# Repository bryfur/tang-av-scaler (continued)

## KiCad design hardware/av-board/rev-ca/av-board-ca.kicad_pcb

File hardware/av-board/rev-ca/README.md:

# AV board rev C-A

The Tang Mega 138K SOM on its own carrier, HDMI from an ADV7511 at up to 1080p60 (rev B's, fed
24-bit RGB 4:4:4). Everything else is shared with rev C-B: [../rev-c/design.md](../rev-c/design.md)
describes both.

Status: designed, reviewed against the data sheets ([../rev-c/review.md](../rev-c/review.md) for
the parts rev C adds; rev B's circuits, shared, in [../rev-b/review.md](../rev-b/review.md)), placed
and routed: DRC clean, no unconnected items, fab files made; not ordered.

- `board.py`: the parts and nets (the shared circuit in ../rev-c/carrier.py and ../kit/circuits.py)
- `gen_pcb.py`: the PCB (../rev-c/layout.py, kit/)
- `fpga/av-board-ca.cst`: the FPGA pin assignment, Gowin constraints, generated from the board

## Ordering at JLCPCB

As rev B ([../rev-b/README.md](../rev-b/README.md)): `fab/` holds the Gerbers and the BOM/CPL, and a
`hand-jacks` BOM/CPL leaves the six RCA jacks for hand soldering. Settings the files do not carry:

- 4 layers, 1.6 mm, stack-up **JLC04161H-7628** (F.Cu / In1 GND / In2 GND / B.Cu), impedance
  control on: the TMDS pairs 0.25 mm lines 0.25 mm apart on F.Cu over In1, 103 R differential by
  IPC-2141, as rev B; confirm in JLCPCB's impedance calculator. The HDMI lines follow TI's
  layout rules (SPRAAR7: ../rev-c/review.md's HDMI rows, checked by `kit/hdmi_audit.py rev-ca`);
  the voids in In1 and In2 under the ESD arrays' TMDS pads are meant.
- Minimum clearance 0.1 mm (the USB-C receptacle's own GND/VBUS pads; JLCPCB's four-layer minimum
  is 0.09 mm); 0.4/0.2 mm vias at the SOM receptacles' ground pads and the ESD arrays.
- Top-side assembly only. Fitted by hand: the SOM's four M2 x 3 mm spacers and M2 screws, the XIAO
  ESP32-S3 (in its sockets J11/J12, its USB-C towards the board's bottom edge: silkscreen
  "XIAO, USB >" beside J12; a C3 works too, JTAG over Wi-Fi only), and the jacks
  for the `hand-jacks` variant.
- Power from a 5 V / 3 A USB-C supply (the board and SOM draw up to about 2 A; a sink with only
  5.1 k on CC cannot ask a weaker source for less). J16 (JTAG) is for a cable with the XIAO out of
  its sockets.
- Check in JLCPCB's preview: the SOM receptacles J20-J22 on their pads (JLCPCB's footprint numbers
  them as a mirror of ours, so its pin 1 dot shows at the far end of the row: the DF40 has no
  polarity [Hirose DF40 drawings], either way is right; do not turn them), the USB-C (mouth out
  of the back edge), the chips' rotations, the RCA jacks' barrels over the back
  edge (the CPL turns the yellow and orange ones 90 degrees for JLCPCB's footprint, kit/gen_fab.py
  JLC_TURN; the red RCJ-012 has no model there and is placed as drawn, as the black RCJ-011).

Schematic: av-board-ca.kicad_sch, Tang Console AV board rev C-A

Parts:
C1, C2: 47u; C_1206_3216Metric; LCSC C96123
C3, C20, C21, C22, C27, C28, C30, C33, C36, C38, C41, C42, C43, C44, C45, C47, C49, C51, C53, C55, C58, C60, C62, C68, C69, C70, C71, C72, C74, C75, C76, C77, C78, C81, C82, C86, C87, C88, C89, C90, C91, C92, C93, C94, C95, C96: 100n; C_0402_1005Metric; LCSC C1525
C4, C6, C7, C9, C10, C12, C13, C15, C73: 10u; C_0805_2012Metric; LCSC C15850
C5: 6.8p; C_0402_1005Metric; LCSC C1576
C8, C11, C14, C64, C66: 220p; C_0402_1005Metric; LCSC C1530
C16, C17, C18, C19, C59, C61, C63, C80, C83, C84, C85: 10u; C_0603_1608Metric; LCSC C19702
C23, C24: 1n; C_0402_1005Metric; LCSC C1523
C25, C26: 33p; C_0402_1005Metric; LCSC C1562
C29, C32, C35, C37: 10u; C_0402_1005Metric; LCSC C15525
C31, C34, C40, C46, C48, C50, C52, C54, C56: 10n; C_0402_1005Metric; LCSC C15195
C39: 82n; C_0402_1005Metric; LCSC C277511
C57, C65, C67, C79: 1u; C_0603_1608Metric; LCSC C15849
C97, C98, C99, C100: 22u; C_0805_2012Metric; LCSC C45783
D1, D3: B5819W; D_SOD-123; LCSC C8598
D2, D4, D5: KT-0603R; LED-SMD_L1.6-W0.8-R-RD; LCSC C2286
D6: SMF5.0A; D_SMF; LCSC C2857263
D7: 1N4148WS; D_SOD-323; LCSC C2128
D8, D9, D10, D11, D12, D13: TPD1E05U06DPYR; X1SON-2_L1.0-W0.6-P0.65-RD-1; LCSC C436349
F1: 3A; Fuse_1812_4532Metric; LCSC C18198349
F2, F3: 0.2A; F0805; LCSC C883105
FB1, FB2, FB3, FB4: 120R; L_0603_1608Metric; LCSC C14709
J1: RCA Y; CONN-TH_RCJ-011; LCSC C4991844
J2: RCA Pb; CONN-TH_RCJ-011; LCSC C4991844
J3: RCA Pr; CONN-TH_RCJ-011; LCSC C4991691
J4: RCA L; CONN-TH_RCJ-011; LCSC C4991844
J5: RCA R; CONN-TH_RCJ-011; LCSC C4991691
J6: HDMI-001; HDMI-SMD_19P-P0.50-H-F; LCSC C138388
J7: SYNC; HDR-TH_2P-P2.54-V-M; LCSC C492401
J8: VGA; HDR-TH_16P-P2.54-V-M-R2-C8-S2.54; LCSC C68234
J11: XIAO 5V..D7; HDR-TH_7P-P2.54-V-F; LCSC C22438157
J12: XIAO D0..D6; HDR-TH_7P-P2.54-V-F; LCSC C22438157
J13: OPTICAL; HDR-TH_3P-P2.54-V-M_PZ254V-11-03P; LCSC C2937625
J14: RCA S/PDIF; CONN-TH_RCJ-011; LCSC C22359757
J15: USB-C 5V; USB-C_SMD-TYPE-C-31-M-12_1; LCSC C165948
J16: JTAG; HDR-TH_6P-P2.54-V-M; LCSC C492405
J20: DF40HC(3.0)-80DS; DF40HC-3.0-80DS-SOM; LCSC C2858577
J21, J22: DF40HC(3.0)-100DS; DF40HC-3.0-100DS-SOM; LCSC C424649
L1: 2.2uH; IND-SMD_L3.0-W3.0_FNR30XXS; LCSC C167747
L2, L3, L4: 10uH; IND-SMD_L4.0-W4.0_SMNR4012; LCSC C222882
Q1, Q2, Q3, Q4: 2N7002; SOT-23-3_L2.9-W1.3-P1.90-LS2.4-BR; LCSC C8545
R1, R2, R101, R102: 5.1k; R_0402_1005Metric; LCSC C25905
R3: 499k; R_0402_1005Metric; LCSC C25793
R4, R53, R55: 100k; R_0402_1005Metric; LCSC C25741
R5: 169k; R_0402_1005Metric; LCSC C25758
R6, R8, R10: 30.1k; R_0402_1005Metric; LCSC C29402
R7, R9: 78.7k; R_0402_1005Metric; LCSC C67239
R11, R12, R13, R14, R32, R33, R34, R50: 75; R_0603_1608Metric; LCSC C4275
R15, R51: 1M; R_0402_1005Metric; LCSC C26083
R16: 1.69k; R_0402_1005Metric; LCSC C25870
R17, R18, R19, R20, R21, R22, R23, R24, R37, R38, R52, R54, R89: 33; R_0402_1005Metric; LCSC C25105
R25, R26, R27, R28, R29, R30, R39, R41, R87, R88: 4.7k; R_0402_1005Metric; LCSC C25900
R31, R35, R36, R43, R44, R45, R47, R49, R60, R61, R62, R63, R64, R65, R66, R67, R68, R69, R70, R71, R72, R73, R74, R75, R76, R78, R80, R81, R85: 10k; R_0402_1005Metric; LCSC C25744
R40, R42: 47k; R_0402_1005Metric; LCSC C25792
R46, R48: 12k; R_0402_1005Metric; LCSC C25752
R56, R57, R58, R59, R77, R79, R82: 470; R_0402_1005Metric; LCSC C25117
R83, R84, R96, R97, R98, R99: 2k; R_0402_1005Metric; LCSC C4109
R86: 27k; R_0402_1005Metric; LCSC C25771
R90, R91, R92, R93, R94: 49.9; R_0402_1005Metric; LCSC C25120
R95: 887; R_0402_1005Metric; LCSC C55968414
R100: 1k; R_0402_1005Metric; LCSC C11702
RN1, RN2, RN3: 33; RES-ARRAY-SMD_0402-8P-L2.0-W1.0-BL; LCSC C25501
SO1, SO2, SO3, SO4: M2 spacer 3mm; SOM-M2-Hole
SW1, SW2, SW3: TS-1187A-B-A-B; SW-SMD_4P-L5.1-W5.1-P3.70-LS6.5-TL_H1.5; LCSC C318884
U1: ADV7181DBCPZ-RL; LFCSP-64_L9.0-W9.0-P0.50-BL-EP7.1; LCSC C514378
U2: ADV7511KSTZ; LQFP-100_L14.0-W14.0-P0.50-LS16.0-BL; LCSC C179459
U3: PCM1808PWR; TSSOP-14_L5.0-W4.4-P0.65-LS6.4-BL; LCSC C55513
U4: TLV62569DBVR; SOT-23-5_L3.0-W1.7-P0.95-LS2.8-BR; LCSC C141836
U5, U6, U7: TPS7A7001DDAR; SOIC-8_L4.9-W3.9-P1.27-LS6.0-BL-EP; LCSC C60719
U8, U9, U10, U19, U20: TPD4E05U06DQAR; USON-10_L2.5-W1.0-P0.50-BL; LCSC C138714
U12: TPS7A2045PDBVR; SOT-23-5_L2.9-W1.6-P0.95-LS2.8-BR; LCSC C2873627
U13: SN74LVC1GU04DBVR; SOT-23-5_L3.0-W1.7-P0.95-LS2.8-BR; LCSC C81934
U14, U15: SN74LVC1G04DBVR; SOT-23-5_L3.0-W1.7-P0.95-LS2.8-BR; LCSC C7827
U17: MS5351M; MSOP-10_L3.0-W3.0-P0.50-LS5.0-BL; LCSC C1509083
U21: SN74LVC2G17DBVR; SOT-23-6_L2.9-W1.6-P0.95-LS2.8-BL; LCSC C10429
U22: SN74LVC8T245PWR; TSSOP-24_L7.8-W4.4-P0.65-LS6.4-BL; LCSC C27643
U23: SN74AVC4T245PWR; TSSOP-16_L5.0-W4.4-P0.65-LS6.4-BL; LCSC C81461
U24: ME6211C30M5G-N; SOT-23-5_L2.9-W1.6-P0.95-LS2.8-BL; LCSC C403651
Y1: 28.63636MHz 20pF; CRYSTAL-SMD_L5.0-W3.2; LCSC C112564
Y2: 25MHz 10pF; CRYSTAL-SMD_4P-L2.0-W1.6-BL; LCSC C5265839

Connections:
1V8A: C11.1, C12.1, D1.2 (A), FB1.1, FB2.1, R7.1, U6.6 (OUT)
1V8B: C14.1, C15.1, L2.1, L3.1, L4.1, R9.1, U7.6 (OUT)
3V0: C80.1, C81.1, U17.1 (VDD), U24.5 (VOUT)
3V3: C8.1, C9.1, C10.1, C13.1, C44.1, C62.1, C63.1, C70.1, C71.1, C72.1, C75.1, C77.1, C79.1, C82.1, C96.1, D1.1 (K), FB3.1, FB4.1, J16.1, Q1.1 (G), Q2.1 (G), R5.1, R25.1, R26.1, R39.1, R41.1, R67.2, R69.2, R70.2, R71.2, R72.2, R73.2, R74.2, R75.1, R76.1, R77.1, R78.1, R79.1, R80.1, R81.1, R86.1, R87.1, R88.1, R96.1, R97.1, R98.1, R100.1, U2.47 (MVDD), U3.4 (VDD), U5.6 (OUT), U6.2 (EN), U6.3 (IN), U7.2 (EN), U7.3 (IN), U13.5 (VCC), U14.5 (VCC), U15.5 (VCC), U17.7 (VDDO), U21.5 (VCC), U22.23 (VCCB), U22.24 (VCCB), U23.16 (VCCB), U24.1 (VIN), U24.3 (CE)
3V6: C5.1, C6.1, C7.1, L1.2, R3.1, U5.2 (EN), U5.3 (IN)
5VA: C60.1, C61.1, U3.3 (VCC), U12.5 (OUT)
+5V: C1.1, C2.1, C3.1, C4.1, C57.1, C97.1, C98.1, C99.1, C100.1, D3.2 (A), F1.2, F2.1, F3.1, J22.89, J22.91, J22.93, J22.95, J22.97, J22.99, U4.1 (EN), U4.4 (VIN), U12.1 (IN), U12.3 (EN)
AIN_PB: C21.2, U1.47 (AIN8)
AIN_PR: C22.2, U1.45 (AIN6)
AIN_VB: C43.2, U1.48 (AIN9)
AIN_VG: C42.2, U1.35 (AIN2)
AIN_VR: C41.2, U1.46 (AIN7)
AIN_Y: C20.2, U1.49 (AIN10)
ALSB: R29.2, U1.52 (ALSB)
AUD_DIV_L: C64.1, C65.1, R46.2, R47.1
AUD_DIV_R: C66.1, C67.1, R48.2, R49.1
AUD_VINL: C65.2, U3.13 (VINL)
AUD_VINR: C67.2, U3.14 (VINR)
AV_AVDD: C18.1, C55.1, C56.1, FB3.2, U1.41 (AVDD)
AV_C0: R21.1, U1.26 (P2)
AV_C1: R20.1, U1.25 (P3)
AV_C2: RN3.3, U1.19 (P4)
AV_C3: RN3.2, U1.18 (P5)
AV_C4: RN3.1, U1.17 (P6)
AV_C5: R19.1, U1.16 (P7)
AV_C6: R18.1, U1.15 (P8)
AV_C7: R17.1, U1.14 (P9)
AV_DE: R24.1, U1.63 (FIELD/DE)
AV_DVDD: C16.1, C49.1, C50.1, C51.1, C52.1, FB1.2, U1.23 (DVDD), U1.58 (DVDD)
AV_DVDDIO: C19.1, C45.1, C46.1, C47.1, C48.1, FB4.2, R28.1, R29.1, R30.1, U1.4 (DVDDIO), U1.11 (DVDDIO)
AV_HS: R22.1, U1.2 (HS/CS)
AV_LLC: RN3.4, U1.20 (LLC)
AV_PVDD: C17.1, C39.2, C40.2, C53.1, C54.1, FB2.2, U1.31 (PVDD)
AV_VS: R23.1, U1.64 (VS)
AV_Y0: RN2.4, U1.8 (P12)
AV_Y1: RN2.3, U1.7 (P13)
AV_Y2: RN2.2, U1.6 (P14)
AV_Y3: RN2.1, U1.5 (P15)
AV_Y4: RN1.4, U1.62 (P16)
AV_Y5: RN1.3, U1.61 (P17)
AV_Y6: RN1.2, U1.60 (P18)
AV_Y7: RN1.1, U1.59 (P19)
CAPC2: C32.1, C33.1, C34.1, U1.44 (CAPC2)
CAPY1: C29.1, C30.1, C31.1, U1.39 (CAPY1)
CAPY2: C27.1, C28.1, C29.2, C30.2, C31.2, C32.2, C33.2, C34.2, U1.40 (CAPY2)
CC1: J15.A5 (CC1), R1.1
CC2: J15.B5 (CC2), R2.1
CEC_PU: D7.2 (A), R86.2
CML: C37.1, C38.1, U1.43 (CML)
D4_A: D4.1 (A), R77.2
D4_K: D4.2 (K), Q3.3 (D)
D5_A: D5.1 (A), R79.2
D5_K: D5.2 (K), Q4.3 (D)
ELPF: C40.1, R16.1, U1.30 (ELPF)
ELPF_RC: C39.1, R16.2
ESP_CS: J22.2, R70.1, U22.18 (B4)
ESP_IRQ: J22.4, R72.1, U23.12 (1B2)
ESP_MISO: J22.14, R74.1, U23.10 (2B2)
ESP_MOSI: J22.16, U22.15 (B7)
ESP_RX: J22.10, R73.1, U23.11 (2B1)
ESP_SCK: J22.12, U22.16 (B6)
ESP_TX: J22.6, U22.17 (B5)
FB_1V8A: C11.2, R7.2, R8.1, U6.7 (FB)
FB_1V8B: C14.2, R9.2, R10.1, U7.7 (FB)
FB_3V3: C8.2, R5.2, R6.1, U5.7 (FB)
FB_3V6: C5.2, R3.2, R4.1, U4.5 (FB)
FMT: R45.1, U3.12 (FMT)
FPGA_DONE: J20.77, Q3.1 (G), R76.2
FPGA_READY: J20.79, Q4.1 (G), R78.2
GND: C1.2, C2.2, C3.2, C4.2, C6.2, C7.2, C9.2, C10.2, C12.2, C13.2, C15.2, C16.2, C17.2, C18.2, C19.2, C25.2, C26.2, C27.2, C28.2, C35.2, C36.2, C37.2, C38.2, C44.2, C45.2, C46.2, C47.2, C48.2, C49.2, C50.2, C51.2, C52.2, C53.2, C54.2, C55.2, C56.2, C57.2, C58.2, C59.2, C60.2, C61.2, C62.2, C63.2, C64.2, C66.2, C68.2, C70.2, C71.2, C72.2, C73.2, C74.2, C75.2, C76.2, C77.2, C78.2, C79.2, C80.2, C81.2, C82.2, C83.2, C84.2, C85.2, C86.2, C87.2, C88.2, C89.2, C90.2, C91.2, C92.2, C93.2, C94.2, C95.2, C96.2, C97.2, C98.2, C99.2, C100.2, D2.2 (K), D6.2 (A), D8.2 (GND), D9.2 (GND), D10.2 (GND), D11.2 (GND), D12.2 (GND), D13.2 (GND), J1.1, J2.1, J3.1, J4.1, J5.1, J6.2 (TMDSData2Shield), J6.5 (TMDSData1Shield), J6.8 (TMDSData0Shield), J6.11 (TMDSClockShield), J6.17 (DDC/CECGround), J6.20, J6.21, J6.22, J6.23, J7.2, J8.5, J8.6, J8.7, J8.8, J8.10, J11.2, J13.2, J14.1, J15.1 (EH), J15.2 (EH), J15.3 (EH), J15.4 (EH), J15.A1B12 (GND), J15.B1A12 (GND), J16.2, J20.1, J20.2, J20.8, J20.11, J20.16, J20.17, J20.21, J20.22, J20.27, J20.35, J20.38, J20.60, J20.63, J20.66, J21.2, J21.3, J21.8, J21.9, J21.14, J21.15, J21.20, J21.21, J21.26, J21.27, J21.32, J21.33, J21.38, J21.39, J21.45, J21.46, J21.51, J21.57, J21.63, J21.69, J21.70, J21.75, J21.76, J21.81, J21.82, J21.87, J21.88, J21.93, J21.94, J21.99, J21.100, J22.47, J22.53, J22.59, J22.65, J22.77, J22.79, J22.81, J22.83, J22.85, J22.87, J22.100, Q3.2 (S), Q4.2 (S), R1.2, R2.2, R4.2, R6.2, R8.2, R10.2, R11.2, R12.2, R13.2, R14.2, R27.2, R31.2, R32.2, R33.2, R34.2, R35.2, R36.2, R43.2, R44.2, R45.2, R47.2, R49.2, R50.2, R53.2, R55.2, R61.2, R66.2, R68.2, R85.2, R95.2, R99.2, R101.2, R102.2, SO1.1, SO2.1, SO3.1, SO4.1, SW1.4 (D), SW2.4 (D), SW3.4 (D), U1.3 (GND), U1.10 (GND), U1.24 (GND), U1.57 (GND), U1.65 (EP), U2.3 (DSD0), U2.4 (DSD1), U2.5 (DSD2), U2.6 (DSD3), U2.7 (DSD4), U2.8 (DSD5), U2.9 (DSDCLK), U2.13 (I2S1), U2.14 (I2S2), U2.15 (I2S3), U2.18 (GND), U2.20 (GND), U2.22 (GND), U2.23 (GND), U2.27 (GND), U2.31 (GND), U2.37 (GND), U2.44 (GND), U2.51 (HEAC-), U2.52 (HEAC+), U2.65 (D27), U2.66 (D26), U2.67 (D25), U2.68 (D24), U2.75 (GND), U2.81 (D15), U2.82 (D14), U2.83 (D13), U2.84 (D12), U2.93 (D3), U2.94 (D2), U2.95 (D1), U2.96 (D0), U2.99 (GND), U2.100 (GND), U3.2 (AGND), U3.5 (DGND), U4.2 (GND), U5.1 (NC), U5.4 (NC), U5.5 (NC), U5.8 (GND), U5.9 (EP), U6.1 (NC), U6.4 (NC), U6.5 (NC), U6.8 (GND), U6.9 (EP), U7.1 (NC), U7.4 (NC), U7.5 (NC), U7.8 (GND), U7.9 (EP), U8.3 (GND), U8.8 (GND), U9.3 (GND), U9.8 (GND), U10.3 (GND), U10.8 (GND), U12.2 (GND), U13.3 (GND), U14.3 (GND), U15.3 (GND), U17.8 (GND), U19.3 (GND), U19.8 (GND), U20.3 (GND), U20.8 (GND), U21.2 (GND), U22.10 (A8), U22.11 (GND), U22.12 (GND), U22.13 (GND), U22.22 (~OE), U23.2 (1DIR), U23.3 (2DIR), U23.8 (GND), U23.9 (GND)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
HDMI_5V: C78.1, F3.2, J6.18 (+5VPower), R83.1, R84.1
HDMI_CEC: D7.1 (K), J6.13 (CEC), U2.48 (CEC), U8.5 (D2-), U8.6 (NC)
HDMI_HPD: J6.19 (HotPlugDetect), R85.1, U2.30 (HPD), U8.4 (D2+), U8.7 (NC)
HDMI_SCL: J6.15 (SCL), R83.2, U2.53 (DDCSCL), U8.1 (D1+), U8.10 (NC)
HDMI_SDA: J6.16 (SDA), R84.2, U2.54 (DDCSDA), U8.2 (D1-), U8.9 (NC)
IN_BCK: J21.67, U3.8 (BCK)
IN_C0: J22.86, R21.2
IN_C1: J22.84, R20.2
IN_C2: J22.82, RN3.6
IN_C3: J22.63, RN3.7
IN_C4: J22.80, RN3.8
IN_C5: J22.78, R19.2
IN_C6: J22.61, R18.2
IN_C7: J22.76, R17.2
IN_DE: J22.56, R24.2
IN_DOUT: J21.65, U3.9 (DOUT)
IN_HS: J22.62, R22.2
IN_INT: J22.60, R28.2, U1.1 (#INT)
IN_KEY1: J21.5, R80.2, SW1.1 (A)
IN_KEY2: J21.7, R81.2, SW2.1 (A)
IN_LED: J21.11, R82.1
IN_LLC: J22.88, RN3.5
IN_LRCK: J21.66, U3.7 (LRCK)
IN_RESET_N: J22.90, R27.1, U1.51 (#RESET)
IN_SCKI: J21.68, U3.6 (SCKI)
IN_SCL: J22.44, R25.2, U1.54 (SCLK)
IN_SDA: J22.42, R26.2, U1.53 (SDATA)
IN_VS: J22.58, R23.2
IN_Y0: J22.74, RN2.5
IN_Y1: J22.68, RN2.6
IN_Y2: J22.66, RN2.7
IN_Y3: J22.64, RN2.8
IN_Y4: J22.54, RN1.5
IN_Y5: J22.52, RN1.6
IN_Y6: J22.48, RN1.7
IN_Y7: J22.46, RN1.8
JTAG_TCK: J16.3, J20.7, R68.1, U22.20 (B2)
JTAG_TDI: J16.5, J20.9, R69.1, U22.19 (B3)
JTAG_TDO: J16.4, J20.5, R71.1, U23.13 (1B1)
JTAG_TMS: J16.6, J20.3, R67.1, U22.21 (B1)
LED_A: D2.1 (A), R82.2
MD0: R43.1, U3.10 (MD0)
MD1: R44.1, U3.11 (MD1)
MODE0: J22.73, R100.2
MODE1: J22.71, R101.1
MODE2: J22.69, R102.1
OUT_B0: J21.17, U2.92 (D4)
OUT_B1: J21.16, U2.91 (D5)
OUT_B2: J21.19, U2.90 (D6)
OUT_B3: J21.23, U2.89 (D7)
OUT_B4: J21.22, U2.88 (D8)
OUT_B5: J21.24, U2.87 (D9)
OUT_B6: J21.29, U2.86 (D10)
OUT_B7: J21.28, U2.85 (D11)
OUT_CECCLK: J21.53, U2.50 (CEC_CLK)
OUT_CLK: J21.35, U2.79 (CLK)
OUT_DE: J21.13, U2.97 (DE)
OUT_G0: J21.30, U2.80 (D16)
OUT_G1: J21.37, U2.78 (D17)
OUT_G2: J21.34, U2.74 (D18)
OUT_G3: J21.36, U2.73 (D19)
OUT_G4: J21.41, U2.72 (D20)
OUT_G5: J21.40, U2.71 (D21)
OUT_G6: J21.42, U2.70 (D22)
OUT_G7: J21.44, U2.69 (D23)
OUT_HSYNC: J21.10, U2.98 (HSYNC)
OUT_I2S0: J20.78, R93.1
OUT_INT: J21.62, R98.2, U2.45 (INT)
OUT_LRCLK: J21.4, R92.1
OUT_MCLK: J20.76, R90.1
OUT_PD: J20.75, R99.1, U2.38 (PD)
OUT_R0: J21.48, U2.64 (D28)
OUT_R1: J21.50, U2.63 (D29)
OUT_R2: J21.52, U2.62 (D30)
OUT_R3: J21.43, U2.61 (D31)
OUT_R4: J21.54, U2.60 (D32)
OUT_R5: J21.56, U2.59 (D33)
OUT_R6: J21.58, U2.58 (D34)
OUT_R7: J21.47, U2.57 (D35)
OUT_SCL: J21.49, R96.2, U2.55 (SCL)
OUT_SCLK: J20.80, R91.1
OUT_SDA: J21.60, R97.2, U2.56 (SDA)
OUT_SPDIF: J20.74, R94.1
OUT_VSYNC: J21.6, U2.2 (VSYNC)
PD_FB: R31.1, U1.32 (FB)
PLL_CLK2: J21.31, R89.2
PLL_CLK2_S: R89.1, U17.6 (CLK2)
PLL_SCL: J21.64, R87.2, U17.4 (SCL)
PLL_SDA: J21.55, R88.2, U17.5 (SDA)
PLL_XA: U17.2 (XA), Y2.1
PLL_XB: U17.3 (XB), Y2.3
PWRDWN: R30.2, U1.29 (#PWRDWN)
RCA_L: J4.2, R46.1
RCA_PB: C21.1, D9.1 (I/O), J2.2, R12.1
RCA_PR: C22.1, D10.1 (I/O), J3.2, R13.1
RCA_R: J5.2, R48.1
RCA_SYNC: C24.1, D11.1 (I/O), J7.1, R14.1
RCA_Y: C20.1, C23.1, D8.1 (I/O), J1.2, R11.1
RECONFIG_N: J20.61, R75.2, SW3.1 (A)
REFOUT: C35.1, C36.1, U1.42 (REFOUT)
R_EXT: R95.1, U2.28 (R_EXT)
SPDIF_5V: C68.1, F2.2, J13.3
SPDIF_AC: C69.2, R51.2, U13.2 (A)
SPDIF_AMP: R51.1, U13.4 (Y), U14.2 (A)
SPDIF_COAX: C69.1, D12.1 (I/O), J14.2, R50.1
SPDIF_OPT: D13.1 (I/O), J13.1, R53.1, U15.2 (A)
SPDIF_ORX: J21.59, R54.2
SPDIF_OSQ: R54.1, U15.4 (Y)
SPDIF_RX: J21.61, R52.2
SPDIF_SQ: R52.1, U14.4 (Y)
SW_3V6: L1.1, U4.3 (SW)
SYNC_G: C24.2, U1.33 (SOG)
SYNC_Y: C23.2, U1.50 (SOY)
TMDS_CK_N: J6.12 (TMDSClock-), U2.32 (TXC-), U10.5 (D2-), U10.6 (NC)
TMDS_CK_P: J6.10 (TMDSClock+), U2.33 (TXC+), U10.4 (D2+), U10.7 (NC)
TMDS_D0_N: J6.9 (TMDSData0-), U2.35 (TX0-), U10.2 (D1-), U10.9 (NC)
TMDS_D0_P: J6.7 (TMDSData0+), U2.36 (TX0+), U10.1 (D1+), U10.10 (NC)
TMDS_D1_N: J6.6 (TMDSData1-), U2.39 (TX1-), U9.5 (D2-), U9.6 (NC)
TMDS_D1_P: J6.4 (TMDSData1+), U2.40 (TX1+), U9.4 (D2+), U9.7 (NC)
TMDS_D2_N: J6.3 (TMDSData2-), U2.42 (TX2-), U9.2 (D1-), U9.9 (NC)
TMDS_D2_P: J6.1 (TMDSData2+), U2.43 (TX2+), U9.1 (D1+), U9.10 (NC)
TX_AVDD: C84.1, C90.1, C91.1, C92.1, C93.1, L3.2, U2.24 (PVDD), U2.25 (PVDD), U2.29 (AVDD), U2.34 (AVDD), U2.41 (AVDD)
TX_DVDD: C83.1, C86.1, C87.1, C88.1, C89.1, L2.2, U2.1 (DVDD), U2.19 (DVDD), U2.49 (DVDD), U2.76 (DVDD), U2.77 (DVDD)
TX_I2S0: R93.2, U2.12 (I2S0)
TX_LRCLK: R92.2, U2.17 (LRCLK)
TX_MCLK: R90.2, U2.11 (MCLK)
TX_PLVDD: C85.1, C94.1, C95.1, L4.2, U2.21 (PLVDD), U2.26 (BGVDD)
TX_SCLK: R91.2, U2.16 (SCLK)
TX_SPDIF: R94.2, U2.10 (SPDIF)
VBUS_IN: D6.1 (K), F1.1, J15.A4B9 (VBUS), J15.B4A9 (VBUS)
VGA_5V: J8.9, R40.1, R42.1
VGA_B: C43.1, J8.3, R34.1, U19.5 (D2-), U19.6 (NC)
VGA_G: C42.1, J8.2, R33.1, U19.2 (D1-), U19.9 (NC)
VGA_HS: J8.13, R35.1, U20.1 (D1+), U20.10 (NC), U21.1 (1A)
VGA_HSB: R37.1, U21.6 (1Y)
VGA_HSIN: R37.2, U1.56 (HS_IN/CS_IN)
VGA_R: C41.1, J8.1, R32.1, U19.4 (D2+), U19.7 (NC)
VGA_SCL: J8.15, Q2.3 (D), R42.2, U20.5 (D2-), U20.6 (NC)
VGA_SCL_F: J22.38, Q2.2 (S), R41.2
VGA_SDA: J8.12, Q1.3 (D), R40.2, U20.4 (D2+), U20.7 (NC)
VGA_SDA_F: J22.40, Q1.2 (S), R39.2
VGA_VS: J8.14, R36.1, U20.2 (D1-), U20.9 (NC), U21.3 (2A)
VGA_VSB: R38.1, U21.4 (2Y)
VGA_VSIN: R38.2, U1.55 (VS_IN)
VREF: C58.1, C59.1, U3.1 (VREF)
XIAO_3V3: C74.1, C76.1, J11.3, R55.1, R60.2, R62.2, R63.2, R64.2, R65.2, U22.1 (VCCA), U22.2 (DIR), U23.1 (VCCA)
XIAO_5V: C73.1, D3.1 (K), J11.1
XIAO_D0: J12.1, R60.1, U22.3 (A1)
XIAO_D1: J12.2, R61.1, U22.4 (A2)
XIAO_D2: J12.3, R62.1, U22.5 (A3)
XIAO_D3: J12.4, R56.2
XIAO_D3_A: R56.1, U23.4 (1A1)
XIAO_D4: J12.5, R63.1, U22.6 (A4)
XIAO_D5: J12.6, R57.2
XIAO_D5_A: R57.1, U23.5 (1A2)
XIAO_D6: J12.7, R64.1, U22.7 (A5)
XIAO_D7: J11.7, R58.2
XIAO_D7_A: R58.1, U23.6 (2A1)
XIAO_D8: J11.6, R65.1, U22.8 (A6)
XIAO_D9: J11.5, R59.2
XIAO_D9_A: R59.1, U23.7 (2A2)
XIAO_D10: J11.4, R66.1, U22.9 (A7)
XTAL: C25.1, R15.1, U1.22 (XTAL), Y1.1 (OSC1)
XTAL1: C26.1, R15.2, U1.21 (XTAL1), Y1.2 (OSC2)

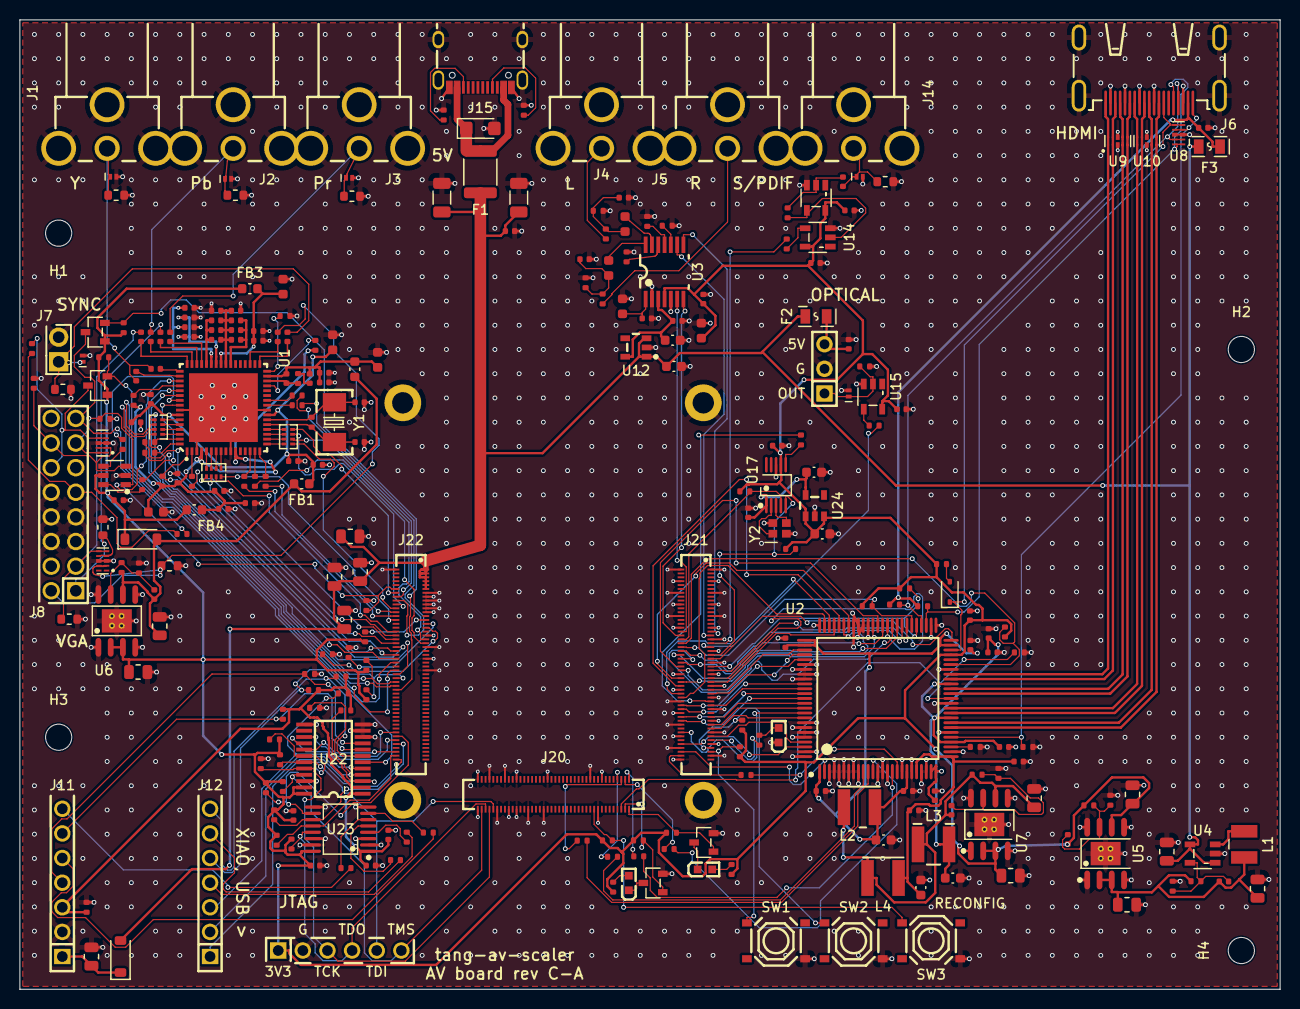
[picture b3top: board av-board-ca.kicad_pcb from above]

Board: 4 copper layers, 130.0 x 100.0 mm, 284 parts (0 on the bottom side), 234 nets.

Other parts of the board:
H1, H2, H3, H4: MountingHole_2.7mm_M2.5

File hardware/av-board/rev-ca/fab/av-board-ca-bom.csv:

Comment,Designator,Footprint,LCSC Part #
10u,"C4,C6,C7,C9,C10,C12,C13,C15,C73",C_0805_2012Metric,C15850
47u,"C1,C2",C_1206_3216Metric,C96123
1n,"C23,C24",C_0402_1005Metric,C1523
33p,"C25,C26",C_0402_1005Metric,C1562
10u,"C29,C32,C35,C37",C_0402_1005Metric,C15525
82n,C39,C_0402_1005Metric,C277511
10n,"C31,C34,C40,C46,C48,C50,C52,C54,C56",C_0402_1005Metric,C15195
6.8p,C5,C_0402_1005Metric,C1576
10u,"C16,C17,C18,C19,C59,C61,C63,C80,C83,C84,C85",C_0603_1608Metric,C19702
220p,"C8,C11,C14,C64,C66",C_0402_1005Metric,C1530
1u,"C57,C65,C67,C79",C_0603_1608Metric,C15849
100n,"C3,C20,C21,C22,C27,C28,C30,C33,C36,C38,C41,C42,C43,C44,C45,C47,C49,C51,C53,C55,C58,C60,C62,C68,C69,C70,C71,C72,C74,C75,C76,C77,C78,C81,C82,C86,C87,C88,C89,C90,C91,C92,C93,C94,C95,C96",C_0402_1005Metric,C1525
22u,"C97,C98,C99,C100",C_0805_2012Metric,C45783
TPD1E05U06DPYR,"D8,D9,D10,D11,D12,D13",X1SON-2_L1.0-W0.6-P0.65-RD-1,C436349
KT-0603R,"D2,D4,D5",LED-SMD_L1.6-W0.8-R-RD,C2286
B5819W,"D1,D3",D_SOD-123,C8598
SMF5.0A,D6,D_SMF,C2857263
1N4148WS,D7,D_SOD-323,C2128
3A,F1,Fuse_1812_4532Metric,C18198349
0.2A,"F2,F3",F0805,C883105
120R,"FB1,FB2,FB3,FB4",L_0603_1608Metric,C14709
RCA Y,J1,CONN-TH_RCJ-011,C4991844
XIAO 5V..D7,J11,HDR-TH_7P-P2.54-V-F,C22438157
XIAO D0..D6,J12,HDR-TH_7P-P2.54-V-F,C22438157
OPTICAL,J13,HDR-TH_3P-P2.54-V-M_PZ254V-11-03P,C2937625
RCA S/PDIF,J14,CONN-TH_RCJ-011,C22359757
USB-C 5V,J15,USB-C_SMD-TYPE-C-31-M-12_1,C165948
JTAG,J16,HDR-TH_6P-P2.54-V-M,C492405
RCA Pb,J2,CONN-TH_RCJ-011,C4991844
DF40HC(3.0)-80DS,J20,DF40HC-3.0-80DS-SOM,C2858577
DF40HC(3.0)-100DS,"J21,J22",DF40HC-3.0-100DS-SOM,C424649
RCA Pr,J3,CONN-TH_RCJ-011,C4991691
RCA L,J4,CONN-TH_RCJ-011,C4991844
RCA R,J5,CONN-TH_RCJ-011,C4991691
HDMI-001,J6,HDMI-SMD_19P-P0.50-H-F,C138388
SYNC,J7,HDR-TH_2P-P2.54-V-M,C492401
VGA,J8,HDR-TH_16P-P2.54-V-M-R2-C8-S2.54,C68234
2.2uH,L1,IND-SMD_L3.0-W3.0_FNR30XXS,C167747
10uH,"L2,L3,L4",IND-SMD_L4.0-W4.0_SMNR4012,C222882
2N7002,"Q1,Q2,Q3,Q4",SOT-23-3_L2.9-W1.3-P1.90-LS2.4-BR,C8545
5.1k,"R1,R2,R101,R102",R_0402_1005Metric,C25905
1k,R100,R_0402_1005Metric,C11702
75,"R11,R12,R13,R14,R32,R33,R34,R50",R_0603_1608Metric,C4275
1.69k,R16,R_0402_1005Metric,C25870
33,"R17,R18,R19,R20,R21,R22,R23,R24,R37,R38,R52,R54,R89",R_0402_1005Metric,C25105
499k,R3,R_0402_1005Metric,C25793
4.7k,"R25,R26,R27,R28,R29,R30,R39,R41,R87,R88",R_0402_1005Metric,C25900
47k,"R40,R42",R_0402_1005Metric,C25792
10k,"R31,R35,R36,R43,R44,R45,R47,R49,R60,R61,R62,R63,R64,R65,R66,R67,R68,R69,R70,R71,R72,R73,R74,R75,R76,R78,R80,R81,R85",R_0402_1005Metric,C25744
12k,"R46,R48",R_0402_1005Metric,C25752
169k,R5,R_0402_1005Metric,C25758
1M,"R15,R51",R_0402_1005Metric,C26083
100k,"R4,R53,R55",R_0402_1005Metric,C25741
30.1k,"R6,R8,R10",R_0402_1005Metric,C29402
470,"R56,R57,R58,R59,R77,R79,R82",R_0402_1005Metric,C25117
2k,"R83,R84,R96,R97,R98,R99",R_0402_1005Metric,C4109
27k,R86,R_0402_1005Metric,C25771
78.7k,"R7,R9",R_0402_1005Metric,C67239
49.9,"R90,R91,R92,R93,R94",R_0402_1005Metric,C25120
887,R95,R_0402_1005Metric,C55968414
33,"RN1,RN2,RN3",RES-ARRAY-SMD_0402-8P-L2.0-W1.0-BL,C25501
TS-1187A-B-A-B,"SW1,SW2,SW3",SW-SMD_4P-L5.1-W5.1-P3.70-LS6.5-TL_H1.5,C318884
ADV7181DBCPZ-RL,U1,LFCSP-64_L9.0-W9.0-P0.50-BL-EP7.1,C514378
TPS7A2045PDBVR,U12,SOT-23-5_L2.9-W1.6-P0.95-LS2.8-BR,C2873627
SN74LVC1GU04DBVR,U13,SOT-23-5_L3.0-W1.7-P0.95-LS2.8-BR,C81934
SN74LVC1G04DBVR,"U14,U15",SOT-23-5_L3.0-W1.7-P0.95-LS2.8-BR,C7827
MS5351M,U17,MSOP-10_L3.0-W3.0-P0.50-LS5.0-BL,C1509083
TPD4E05U06DQAR,"U8,U9,U10,U19,U20",USON-10_L2.5-W1.0-P0.50-BL,C138714
ADV7511KSTZ,U2,LQFP-100_L14.0-W14.0-P0.50-LS16.0-BL,C179459
SN74LVC2G17DBVR,U21,SOT-23-6_L2.9-W1.6-P0.95-LS2.8-BL,C10429
SN74LVC8T245PWR,U22,TSSOP-24_L7.8-W4.4-P0.65-LS6.4-BL,C27643
SN74AVC4T245PWR,U23,TSSOP-16_L5.0-W4.4-P0.65-LS6.4-BL,C81461
ME6211C30M5G-N,U24,SOT-23-5_L2.9-W1.6-P0.95-LS2.8-BL,C403651
PCM1808PWR,U3,TSSOP-14_L5.0-W4.4-P0.65-LS6.4-BL,C55513
TLV62569DBVR,U4,SOT-23-5_L3.0-W1.7-P0.95-LS2.8-BR,C141836
TPS7A7001DDAR,"U5,U6,U7",SOIC-8_L4.9-W3.9-P1.27-LS6.0-BL-EP,C60719
28.63636MHz 20pF,Y1,CRYSTAL-SMD_L5.0-W3.2,C112564
25MHz 10pF,Y2,CRYSTAL-SMD_4P-L2.0-W1.6-BL,C5265839

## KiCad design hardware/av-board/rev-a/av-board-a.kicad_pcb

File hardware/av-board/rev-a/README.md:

# AV board rev A

The ADV7842 board: component video into an ADV7842 (256-ball BGA, 1.0 mm pitch), stereo audio
into a PCM1808, HDMI out of an ADV7511. Six layers.

Status: routed (Freerouting, mazeroute.py, the TMDS pairs refined on DeepPCB), DRC clean, fab
files made; not ordered. JLCPCB quoted about $400 for it, most of that the BGA (and the six
layers its escape needs: four did not route). Rev B replaces the ADV7842 with the ADV7181D.

- [design.md](design.md): the electrical design, connection by connection, with its sources
- [reference-notes.md](reference-notes.md): what ADI's and TI's reference designs say
- `board.py`, `gen_pcb.py`: the sources; made as in [../README.md](../README.md)

## Ordering at JLCPCB

`fab/av-board-a-gerbers.zip` for the board, `fab/av-board-a-bom.csv` and `fab/av-board-a-cpl.csv`
for assembly. Settings the files do not carry:

- 6 layers, 1.6 mm, stack-up **JLC06161H-7628B** (the TMDS geometry assumes its 0.218 mm 7628
  prepreg under the outer layers); impedance control on: the TMDS pairs are 0.2 mm with 0.15 mm
  gap on the outer layers, about 100 R differential. Confirm in JLCPCB's impedance calculator.
- Via 0.3 mm drill / 0.5 mm pad, minimum track and space 0.127 mm.
- Assembly on both sides (83 of 229 parts are on the bottom), including the through-hole parts
  (J9/J10 sockets on the bottom, RCA jacks, HDMI). The ADV7842 is a 1.0 mm-pitch BGA.
- Check every part's rotation in JLCPCB's placement preview: its library sometimes turns a part
  90 or 180 degrees from KiCad's.
- TEST8's pull-down (DNP) is left out of the BOM on purpose (design.md).

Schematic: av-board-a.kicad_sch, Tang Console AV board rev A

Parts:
C1, C2: 22u; C_0805_2012Metric; LCSC C45783
C3, C32, C33, C34, C38, C39, C43, C44, C71, C103, C104, C106, C108, C114, C115, C116, C117, C118, C119, C120, C121, C122, C123, C124, C125: 100n; C_0402_1005Metric; LCSC C1525
C4, C5, C8, C11, C12, C14, C15: 10u; C_0805_2012Metric; LCSC C15850
C6, C13, C16, C45, C46, C47, C48, C49, C50, C51, C52, C53, C59, C60, C61, C62, C63, C64, C65, C66, C67, C77, C78, C89, C90, C91, C92, C93, C94, C95, C96, C97, C98, C99, C100, C101, C110, C112: 220p; C_0402_1005Metric; LCSC C1530
C7: 4.7u; C_0805_2012Metric; LCSC C1779
C9: 6.8p; C_0402_1005Metric; LCSC C1576
C10: 470n; C_0603_1608Metric; LCSC C1623
C17, C19, C21, C23, C25, C27: 33u; CAP-SMD_L3.5-W2.8-R-RD; LCSC C7202
C18, C20, C22, C24, C26, C28, C29, C30, C31, C40, C105, C107, C109: 10u; C_0603_1608Metric; LCSC C19702
C35: 1n; C_0402_1005Metric; LCSC C1523
C36, C37: 30p; C_0402_1005Metric; LCSC C1570
C41, C42, C54, C55, C56, C57, C58, C68, C69, C70, C72, C73, C74, C75, C76, C79, C80, C81, C82, C83, C84, C85, C86, C87, C88, C102: 10n; C_0402_1005Metric; LCSC C15195
C111, C113: 1u; C_0603_1608Metric; LCSC C15849
F1: 0.2A; F0805; LCSC C883105
FB1: 600R; L_0603_1608Metric; LCSC C1002
FL1, FL2, FL3, FL4, FL5, FL6: NFE61PT472C1H9L; FILTER-SMD_NFE61PT472C1H9L; LCSC C79933
J1: RCA Y; CONN-TH_RCJ-011; LCSC C4992678
J2: RCA Pb; CONN-TH_RCJ-011; LCSC C4992678
J3: RCA Pr; CONN-TH_RCJ-011; LCSC C4991691
J4: RCA L; CONN-TH_RCJ-011; LCSC C4992678
J5: RCA R; CONN-TH_RCJ-011; LCSC C4991691
J6: HDMI-001; HDMI-SMD_19P-P0.50-H-F; LCSC C138388
J9, J10: 2x20 socket; HDR-TH_40P-P2.54-V-F-R2-C20-S2.54-2; LCSC C5124634
L1: 2.2uH; IND-SMD_L3.0-W3.0_FNR30XXS; LCSC C167747
L2, L3, L4: 10uH; IND-SMD_L4.0-W4.0_SMNR4012; LCSC C222882
R1, R2, R27, R28, R29, R30, R49, R50, R51, R52, R53, R54, R55, R67: 10k; R_0402_1005Metric; LCSC C25744
R3: 169k; R_0402_1005Metric; LCSC C25758
R4, R9, R11: 30.1k; R_0402_1005Metric; LCSC C29402
R5: 316k; R_0402_1005Metric; LCSC C25777
R6, R7: 100k; R_0402_1005Metric; LCSC C25741
R8, R10: 78.7k; R_0402_1005Metric; LCSC C67239
R12, R14, R16: 24; R_0402_1005Metric; LCSC C2909340
R13, R15, R17, R56, R57, R58, R59: 51; R_0402_1005Metric; LCSC C25125
R18: 390k; R_0402_1005Metric; LCSC C2909352
R19: 499; R_0402_1005Metric; LCSC C4125
R20, R21, R22, R23, R24, R25, R31, R32, R33, R34, R35, R36, R37, R38, R39, R40, R41, R42, R43, R44, R45, R46, R47, R48: 4.7k; R_0402_1005Metric; LCSC C25900
R26: 4.7k; R_0402_1005Metric; LCSC C25900; not fitted
R60: 887; R_0402_1005Metric; LCSC C55968414
R61, R62, R63, R64, R65, R66: 2k; R_0402_1005Metric; LCSC C4109
RN1, RN2, RN3, RN4, RN5: 75; RES-ARRAY-SMD_0402-8P-L2.0-W1.0-BL; LCSC C39128
SW1, SW2: TS-1187A-B-A-B; SW-SMD_4P-L5.1-W5.1-P3.70-LS6.5-TL_H1.5; LCSC C318884
U1: ADV7842KBCZ-5; CSPBGA-256_L17.0-W17.0-R16-C16-P1.00-BL; LCSC C514382
U2: ADV7511KSTZ; LQFP-100_L14.0-W14.0-P0.50-LS16.0-BL; LCSC C179459
U3: PCM1808PWR; TSSOP-14_L5.0-W4.4-P0.65-LS6.4-BL; LCSC C55513
U4: TLV62569DBVR; SOT-23-5_L3.0-W1.7-P0.95-LS2.8-BR; LCSC C141836
U5, U6, U7: TPS7A7001DDAR; SOIC-8_L4.9-W3.9-P1.27-LS6.0-BL-EP; LCSC C60719
U8, U9, U10: TPD4E05U06DQAR; USON-10_L2.5-W1.0-P0.50-BL; LCSC C138714
Y1: 28.63636MHz 20pF; CRYSTAL-SMD_L5.0-W3.2; LCSC C362486

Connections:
1V8A: C12.1, C13.1, FL1.1 (IN), FL2.1 (IN), FL3.1 (IN), FL4.1 (IN), R8.1, U6.6 (OUT)
1V8B: C15.1, C16.1, L2.1, L3.1, L4.1, R10.1, U7.6 (OUT)
2V5: C8.1, C9.1, C11.1, C14.1, L1.2, R5.1, R7.1, U6.3 (IN), U7.3 (IN)
3V3: C5.1, C6.1, C108.1, C109.1, C124.1, FL5.1 (IN), FL6.1 (IN), R1.1, R2.1, R3.1, R20.1, R21.1, R23.1, R24.1, R25.1, R61.1, R62.1, R63.1, U2.47 (MVDD), U3.4 (VDD), U5.6 (OUT)
5VA: C106.1, C107.1, FB1.2, U3.3 (VCC)
+5V: C1.1, C2.1, C3.1, C4.1, C7.1, F1.1, FB1.1, J9.11, J10.11, U1.C8 (RXB_5V), U1.C9 (RXA_5V), U4.1 (EN), U4.4 (VIN), U5.2 (EN), U5.3 (IN)
AIN_PB: C33.2, U1.J13 (AIN6)
AIN_PR: C34.2, U1.K13 (AIN5)
AIN_Y: C32.2, U1.J14 (AIN4)
AUD_DIV_L: C110.1, C111.1, R52.2, R53.1
AUD_DIV_R: C112.1, C113.1, R54.2, R55.1
AUD_VINL: C111.2, U3.13 (VINL)
AUD_VINR: C113.2, U3.14 (VINR)
AV_AVDD: C19.1, C20.1, C54.1, C55.1, C56.1, C57.1, C58.1, C59.1, C60.1, C61.1, C62.1, C63.1, C64.1, C65.1, C66.1, C67.1, FL2.3 (OUT), U1.F12 (AVDD), U1.G12 (AVDD), U1.H12 (AVDD), U1.J12 (AVDD), U1.K12 (AVDD), U1.L12 (AVDD)
AV_C0: RN1.1, U1.B2 (P4)
AV_C1: RN1.2, U1.B1 (P5)
AV_C2: RN1.3, U1.C2 (P6)
AV_C3: RN1.4, U1.C1 (P7)
AV_C4: RN2.3, U1.D2 (P8)
AV_C5: RN2.4, U1.D1 (P9)
AV_C6: RN3.2, U1.E2 (P10)
AV_C7: RN3.3, U1.F2 (P11)
AV_CVDD: C21.1, C22.1, C68.1, C69.1, C70.1, C71.1, FL3.3 (OUT), U1.C12 (CVDD), U1.C13 (CVDD), U1.C14 (CVDD), U1.D12 (CVDD), U1.E11 (CVDD), U1.E12 (CVDD)
AV_DE: RN3.1, U1.D4 (FIELD/DE)
AV_DVDDIO: C25.1, C26.1, C79.1, C80.1, C81.1, C82.1, C83.1, C84.1, C85.1, C86.1, C87.1, C88.1, C89.1, C90.1, C91.1, C92.1, C93.1, C94.1, C95.1, C96.1, C97.1, C98.1, C99.1, C100.1, C101.1, FL5.3 (OUT), U1.F5 (DVDDIO), U1.G5 (DVDDIO), U1.H5 (DVDDIO), U1.J5 (DVDDIO), U1.K5 (DVDDIO), U1.L5 (DVDDIO), U1.M5 (DVDDIO), U1.M6 (VDD_SDRAM), U1.M7 (VDD_SDRAM), U1.M8 (VDD_SDRAM), U1.M9 (VDD_SDRAM), U1.M10 (VDD_SDRAM)
AV_HS: RN2.2, U1.C4 (HS/CS)
AV_LLC: RN5.4, U1.N1 (LLC)
AV_PVDD: C23.1, C24.1, C102.1, C103.1, FL4.3 (OUT), U1.D15 (PVDD), U1.D16 (PVDD)
AV_TVDD: C27.1, C28.1, C41.1, C42.1, C43.1, C44.1, C45.1, C46.1, C47.1, C48.1, C49.1, C50.1, C51.1, C52.1, C53.1, FL6.3 (OUT), U1.A5 (TVDD), U1.A15 (TVDD), U1.B5 (TVDD), U1.B15 (TVDD)
AV_VDD: C17.1, C18.1, C72.1, C73.1, C74.1, C75.1, C76.1, C77.1, C78.1, FL1.3 (OUT), U1.J7 (VDD), U1.K6 (VDD), U1.K7 (VDD), U1.K8 (VDD), U1.K9 (VDD), U1.L6 (VDD), U1.L7 (VDD), U1.L8 (VDD), U1.L9 (VDD)
AV_VS: RN2.1, U1.C3 (VS/FIELD)
AV_Y0: RN3.4, U1.H1 (P16)
AV_Y1: RN4.1, U1.J2 (P17)
AV_Y2: RN4.2, U1.J1 (P18)
AV_Y3: RN4.3, U1.K2 (P19)
AV_Y4: RN4.4, U1.K1 (P20)
AV_Y5: RN5.1, U1.L2 (P21)
AV_Y6: RN5.2, U1.L1 (P22)
AV_Y7: RN5.3, U1.M2 (P23)
EN_1V8: C10.1, R7.2, U6.2 (EN), U7.2 (EN)
FB_1V8A: C13.2, R8.2, R9.1, U6.7 (FB)
FB_1V8B: C16.2, R10.2, R11.1, U7.7 (FB)
FB_2V5: C9.2, R5.2, R6.1, U4.5 (FB)
FB_3V3: C6.2, R3.2, R4.1, U5.7 (FB)
FMT: R51.1, U3.12 (FMT)
GND: C1.2, C2.2, C3.2, C4.2, C5.2, C7.2, C8.2, C10.2, C11.2, C12.2, C14.2, C15.2, C17.2, C18.2, C19.2, C20.2, C21.2, C22.2, C23.2, C24.2, C25.2, C26.2, C27.2, C28.2, C29.2, C30.2, C31.2, C36.2, C37.2, C38.2, C39.2, C41.2, C42.2, C43.2, C44.2, C45.2, C46.2, C47.2, C48.2, C49.2, C50.2, C51.2, C52.2, C53.2, C54.2, C55.2, C56.2, C57.2, C58.2, C59.2, C60.2, C61.2, C62.2, C63.2, C64.2, C65.2, C66.2, C67.2, C68.2, C69.2, C70.2, C71.2, C72.2, C73.2, C74.2, C75.2, C76.2, C77.2, C78.2, C79.2, C80.2, C81.2, C82.2, C83.2, C84.2, C85.2, C86.2, C87.2, C88.2, C89.2, C90.2, C91.2, C92.2, C93.2, C94.2, C95.2, C96.2, C97.2, C98.2, C99.2, C100.2, C101.2, C102.2, C103.2, C104.2, C105.2, C106.2, C107.2, C108.2, C109.2, C110.2, C112.2, C114.2, C115.2, C116.2, C117.2, C118.2, C119.2, C120.2, C121.2, C122.2, C123.2, C124.2, C125.2, FL1.2 (GND), FL2.2 (GND), FL3.2 (GND), FL4.2 (GND), FL5.2 (GND), FL6.2 (GND), J1.1, J2.1, J3.1, J4.1, J5.1, J6.2 (TMDSData2Shield), J6.5 (TMDSData1Shield), J6.8 (TMDSData0Shield), J6.11 (TMDSClockShield), J6.17 (DDC/CECGround), J6.20, J6.21, J6.22, J6.23, J9.12, J9.31, J9.32, J9.33, J9.34, J9.35, J9.36, J10.12, J10.27, J10.28, J10.29, J10.30, J10.33, J10.34, J10.35, J10.36, J10.37, J10.38, J10.39, J10.40, R4.2, R6.2, R9.2, R11.2, R13.2, R15.2, R17.2, R19.2, R22.2, R26.2, R27.2, R28.2, R29.2, R30.2, R31.2, R32.2, R33.2, R34.2, R35.2, R36.2, R37.2, R38.2, R39.2, R40.2, R41.2, R42.2, R43.2, R44.2, R45.2, R46.2, R47.2, R48.2, R49.2, R50.2, R51.2, R53.2, R55.2, R60.2, R64.2, R67.2, SW1.4 (D), SW2.4 (D), U1.A1 (GND), U1.A10 (GND), U1.A16 (GND), U1.B10 (GND), U1.C5 (GND), U1.C15 (GND), U1.D5 (GND), U1.E1 (GND), U1.E5 (GND), U1.E6 (GND), U1.E7 (GND), U1.E8 (GND), U1.E9 (GND), U1.E10 (GND), U1.F6 (GND), U1.F7 (GND), U1.F8 (GND), U1.F9 (GND), U1.F10 (GND), U1.F11 (GND), U1.F15 (TRI4), U1.G6 (GND), U1.G7 (GND), U1.G8 (GND), U1.G9 (GND), U1.G10 (GND), U1.G11 (GND), U1.G14 (SYNC4), U1.H6 (GND), U1.H7 (GND), U1.H8 (GND), U1.H9 (GND), U1.H10 (GND), U1.H11 (GND), U1.H16 (SYNC3), U1.J6 (GND), U1.J8 (GND), U1.J9 (GND), U1.J10 (GND), U1.J11 (GND), U1.J16 (GND), U1.K10 (GND), U1.K11 (GND), U1.L10 (GND), U1.L11 (GND), U1.M1 (GND), U1.M11 (GND), U1.M12 (GND), U1.M13 (GND), U1.M14 (GND), U1.M15 (GND), U1.M16 (GND), U1.N4 (TEST4), U1.P3 (TEST5), U1.P13 (SDRAM_VREF), U1.T1 (GND), U1.T6 (GND), U1.T12 (GND), U1.T16 (GND), U2.3 (DSD0), U2.4 (DSD1), U2.5 (DSD2), U2.6 (DSD3), U2.7 (DSD4), U2.8 (DSD5), U2.9 (DSDCLK), U2.10 (SPDIF), U2.13 (I2S1), U2.14 (I2S2), U2.15 (I2S3), U2.18 (GND), U2.20 (GND), U2.22 (GND), U2.23 (GND), U2.27 (GND), U2.31 (GND), U2.37 (GND), U2.44 (GND), U2.48 (CEC), U2.50 (CEC_CLK), U2.51 (HEAC-), U2.52 (HEAC+), U2.57 (D35), U2.58 (D34), U2.59 (D33), U2.60 (D32), U2.61 (D31), U2.62 (D30), U2.63 (D29), U2.64 (D28), U2.65 (D27), U2.66 (D26), U2.67 (D25), U2.68 (D24), U2.75 (GND), U2.89 (D7), U2.90 (D6), U2.91 (D5), U2.92 (D4), U2.93 (D3)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
HDMI_5V: C125.1, F1.2, J6.18 (+5VPower), R65.1, R66.1, U8.5 (D2-), U8.6 (NC)
HDMI_HPD: J6.19 (HotPlugDetect), R67.1, U2.30 (HPD), U8.4 (D2+), U8.7 (NC)
HDMI_SCL: J6.15 (SCL), R65.2, U2.53 (DDCSCL), U8.1 (D1+), U8.10 (NC)
HDMI_SDA: J6.16 (SDA), R66.2, U2.54 (DDCSDA), U8.2 (D1-), U8.9 (NC)
IN_BCK: J9.40, U3.8 (BCK)
IN_C0: J10.1, RN1.8
IN_C1: J10.2, RN1.7
IN_C2: J10.3, RN1.6
IN_C3: J10.4, RN1.5
IN_C4: J10.7, RN2.6
IN_C5: J10.8, RN2.5
IN_C6: J10.10, RN3.7
IN_C7: J10.13, RN3.6
IN_DE: J10.9, RN3.8
IN_DOUT: J9.39, U3.9 (DOUT)
IN_HS: J10.6, RN2.7
IN_INT1: J10.24, R23.2, U1.M4 (INT1)
IN_KEY1: J10.31, R1.2, SW1.1 (A)
IN_KEY2: J10.32, R2.2, SW2.1 (A)
IN_LLC: J10.20, RN5.5
IN_LRCK: J9.38, U3.7 (LRCK)
IN_RESET_N: J10.26, R22.1, U1.N5 (~RESET)
IN_SCKI: J9.37, U3.6 (SCKI)
IN_SCL: J10.23, R20.2, U1.L3 (SCL)
IN_SDA: J10.25, R21.2, U1.M3 (SDA)
IN_VS: J10.5, RN2.8
IN_Y0: J10.14, RN3.5
IN_Y1: J10.15, RN4.8
IN_Y2: J10.16, RN4.7
IN_Y3: J10.17, RN4.6
IN_Y4: J10.18, RN4.5
IN_Y5: J10.19, RN5.8
IN_Y6: J10.21, RN5.7
IN_Y7: J10.22, RN5.6
MD0: R49.1, U3.10 (MD0)
MD1: R50.1, U3.11 (MD1)
OUT_C0: J9.15, U2.80 (D16)
OUT_C1: J9.13, U2.78 (D17)
OUT_C2: J9.10, U2.74 (D18)
OUT_C3: J9.9, U2.73 (D19)
OUT_C4: J9.8, U2.72 (D20)
OUT_C5: J9.7, U2.71 (D21)
OUT_C6: J9.6, U2.70 (D22)
OUT_C7: J9.5, U2.69 (D23)
OUT_CLK: J9.14, U2.79 (CLK)
OUT_DE: J9.24, U2.97 (DE)
OUT_HSYNC: J9.25, U2.98 (HSYNC)
OUT_I2S0: J9.28, R59.1
OUT_INT: J9.2, R63.2, U2.45 (INT)
OUT_LRCLK: J9.30, R58.1
OUT_MCLK: J9.27, R56.1
OUT_PD: J9.1, R64.1, U2.38 (PD)
OUT_SCL: J9.3, R61.2, U2.55 (SCL)
OUT_SCLK: J9.29, R57.1
OUT_SDA: J9.4, R62.2, U2.56 (SDA)
OUT_VSYNC: J9.26, U2.2 (VSYNC)
OUT_Y0: J9.23, U2.88 (D8)
OUT_Y1: J9.22, U2.87 (D9)
OUT_Y2: J9.21, U2.86 (D10)
OUT_Y3: J9.20, U2.85 (D11)
OUT_Y4: J9.19, U2.84 (D12)
OUT_Y5: J9.18, U2.83 (D13)
OUT_Y6: J9.17, U2.82 (D14)
OUT_Y7: J9.16, U2.81 (D15)
PD_DDCA_SCL: R28.1, U1.D10 (DDCA_SCL)
PD_DDCB_SCL: R27.1, U1.D8 (DDCB_SCL)
PD_SDRAM_DQ0: R31.1, U1.R13 (SDRAM_DQ0)
PD_SDRAM_DQ1: R32.1, U1.T13 (SDRAM_DQ1)
PD_SDRAM_DQ2: R33.1, U1.R12 (SDRAM_DQ2)
PD_SDRAM_DQ3: R34.1, U1.P12 (SDRAM_DQ3)
PD_SDRAM_DQ4: R35.1, U1.N12 (SDRAM_DQ4)
PD_SDRAM_DQ5: R36.1, U1.T11 (SDRAM_DQ5)
PD_SDRAM_DQ6: R37.1, U1.R11 (SDRAM_DQ6)
PD_SDRAM_DQ7: R38.1, U1.P11 (SDRAM_DQ7)
PD_SDRAM_DQ8: R39.1, U1.R16 (SDRAM_DQ8)
PD_SDRAM_DQ9: R40.1, U1.R15 (SDRAM_DQ9)
PD_SDRAM_DQ10: R41.1, U1.T15 (SDRAM_DQ10)
PD_SDRAM_DQ11: R42.1, U1.N14 (SDRAM_DQ11)
PD_SDRAM_DQ12: R43.1, U1.P14 (SDRAM_DQ12)
PD_SDRAM_DQ13: R44.1, U1.R14 (SDRAM_DQ13)
PD_SDRAM_DQ14: R45.1, U1.T14 (SDRAM_DQ14)
PD_SDRAM_DQ15: R46.1, U1.N13 (SDRAM_DQ15)
PD_SDRAM_LDQS: R47.1, U1.N11 (SDRAM_LDQS)
PD_SDRAM_UDQS: R48.1, U1.P15 (SDRAM_UDQS)
PD_TTX_SCL: R30.1, U1.F4 (TTX_SCL)
PD_VGA_SCL: R29.1, U1.D13 (VGA_SCL)
PWRDN1: R24.2, U1.C10 (~PWRDN1)
RCA_L: J4.2, R52.1
RCA_PB: J2.2, R14.1
RCA_PR: J3.2, R16.1
RCA_R: J5.2, R54.1
RCA_Y: J1.2, R12.1
REFN: C39.1, C40.2, U1.E16 (REFN)
REFP: C38.1, C40.1, U1.E15 (REFP)
RTERM: R19.1, U1.D11 (RTERM)
R_EXT: R60.1, U2.28 (R_EXT)
SW_2V5: L1.1, U4.3 (SW)
SYNC_Y: C35.2, U1.J15 (SYNC2)
TERM_PB: C33.1, R14.2, R15.1
TERM_PR: C34.1, R16.2, R17.1
TERM_Y: C32.1, C35.1, R12.2, R13.1
TEST8: R25.2, R26.1, U1.C11 (TEST8)
TMDS_CK_N: J6.12 (TMDSClock-), U2.32 (TXC-), U10.5 (D2-), U10.6 (NC)
TMDS_CK_P: J6.10 (TMDSClock+), U2.33 (TXC+), U10.4 (D2+), U10.7 (NC)
TMDS_D0_N: J6.9 (TMDSData0-), U2.35 (TX0-), U10.2 (D1-), U10.9 (NC)
TMDS_D0_P: J6.7 (TMDSData0+), U2.36 (TX0+), U10.1 (D1+), U10.10 (NC)
TMDS_D1_N: J6.6 (TMDSData1-), U2.39 (TX1-), U9.5 (D2-), U9.6 (NC)
TMDS_D1_P: J6.4 (TMDSData1+), U2.40 (TX1+), U9.4 (D2+), U9.7 (NC)
TMDS_D2_N: J6.3 (TMDSData2-), U2.42 (TX2-), U9.2 (D1-), U9.9 (NC)
TMDS_D2_P: J6.1 (TMDSData2+), U2.43 (TX2+), U9.1 (D1+), U9.10 (NC)
TX_AVDD: C30.1, C118.1, C119.1, C120.1, C121.1, L3.2, U2.24 (PVDD), U2.25 (PVDD), U2.29 (AVDD), U2.34 (AVDD), U2.41 (AVDD)
TX_DVDD: C29.1, C114.1, C115.1, C116.1, C117.1, L2.2, U2.1 (DVDD), U2.19 (DVDD), U2.49 (DVDD), U2.76 (DVDD), U2.77 (DVDD)
TX_I2S0: R59.2, U2.12 (I2S0)
TX_LRCLK: R58.2, U2.17 (LRCLK)
TX_MCLK: R56.2, U2.11 (MCLK)
TX_PLVDD: C31.1, C122.1, C123.1, L4.2, U2.21 (PLVDD), U2.26 (BGVDD)
TX_SCLK: R57.2, U2.16 (SCLK)
VREF: C104.1, C105.1, U3.1 (VREF)
XTALN: C37.1, R18.2, U1.C16 (XTALN), Y1.2 (OSC2)
XTALP: C36.1, R18.1, U1.B16 (XTALP), Y1.1 (OSC1)
